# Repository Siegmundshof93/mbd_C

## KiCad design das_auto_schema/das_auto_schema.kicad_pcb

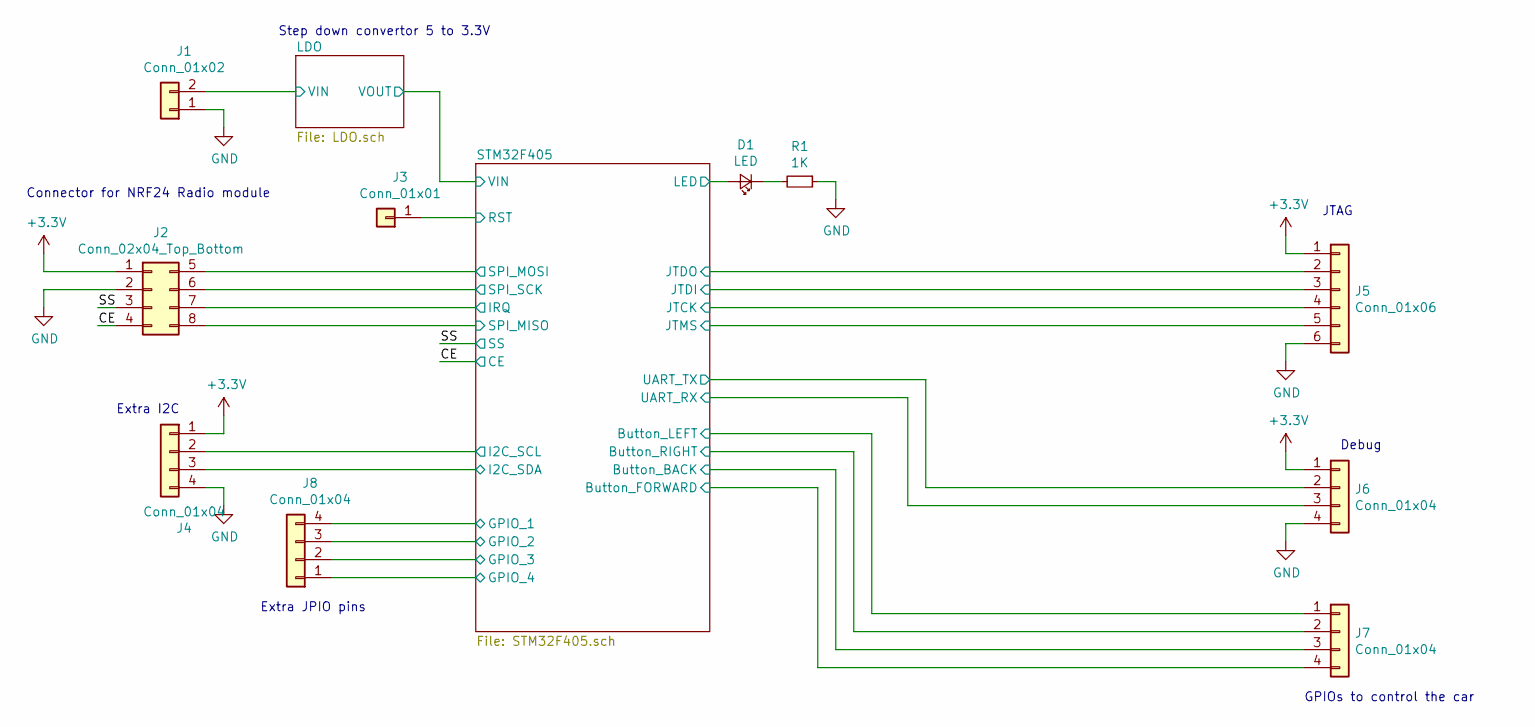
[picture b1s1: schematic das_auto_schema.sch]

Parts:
D1: LED; R_1206_3216Metric
J1: Conn_01x02; PinSocket_1x02_P2.54mm_Vertical
J2: Conn_02x04_Top_Bottom; PinSocket_2x04_P2.54mm_Vertical
J3: Conn_01x01; PinSocket_1x01_P2.54mm_Vertical
J4, J6, J7, J8: Conn_01x04; PinSocket_1x04_P2.54mm_Vertical
J5: Conn_01x06; PinSocket_1x06_P2.54mm_Vertical
R1: 1K; R_0805_2012Metric

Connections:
+3V3: J2.1, J4.1, J5.1, J6.1; also elsewhere on the board
/CE: J2.4; also elsewhere on the board
/LDO/VIN: J1.2; also elsewhere on the board
/SS: J2.3; also elsewhere on the board
/STM32F405/Button_BACK: J7.3; also elsewhere on the board
/STM32F405/Button_FORWARD: J7.4; also elsewhere on the board
/STM32F405/Button_LEFT: J7.1; also elsewhere on the board
/STM32F405/Button_RIGHT: J7.2; also elsewhere on the board
/STM32F405/GPIO_1: J8.4; also elsewhere on the board
/STM32F405/GPIO_2: J8.3; also elsewhere on the board
/STM32F405/GPIO_3: J8.2; also elsewhere on the board
/STM32F405/GPIO_4: J8.1; also elsewhere on the board
/STM32F405/I2C_SCL: J4.2; also elsewhere on the board
/STM32F405/I2C_SDA: J4.3; also elsewhere on the board
/STM32F405/IRQ: J2.7; also elsewhere on the board
/STM32F405/JTCK: J5.4; also elsewhere on the board
/STM32F405/JTDI: J5.3; also elsewhere on the board
/STM32F405/JTDO: J5.2; also elsewhere on the board
/STM32F405/JTMS: J5.5; also elsewhere on the board
/STM32F405/LED: D1.2 (A); also elsewhere on the board
/STM32F405/RST: J3.1; also elsewhere on the board
/STM32F405/SPI_MISO: J2.8; also elsewhere on the board
/STM32F405/SPI_MOSI: J2.5; also elsewhere on the board
/STM32F405/SPI_SCK: J2.6; also elsewhere on the board
/STM32F405/UART_RX: J6.3; also elsewhere on the board
/STM32F405/UART_TX: J6.2; also elsewhere on the board
GND: J1.1, J2.2, J4.4, J5.6, J6.4, R1.1; also elsewhere on the board
unnamed: D1.1 (K), R1.2

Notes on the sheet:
Connector for NRF24 Radio module
JTAG
Extra JPIO pins
GPIOs to control the car
Debug
Step down convertor 5 to 3.3V
Extra I2C

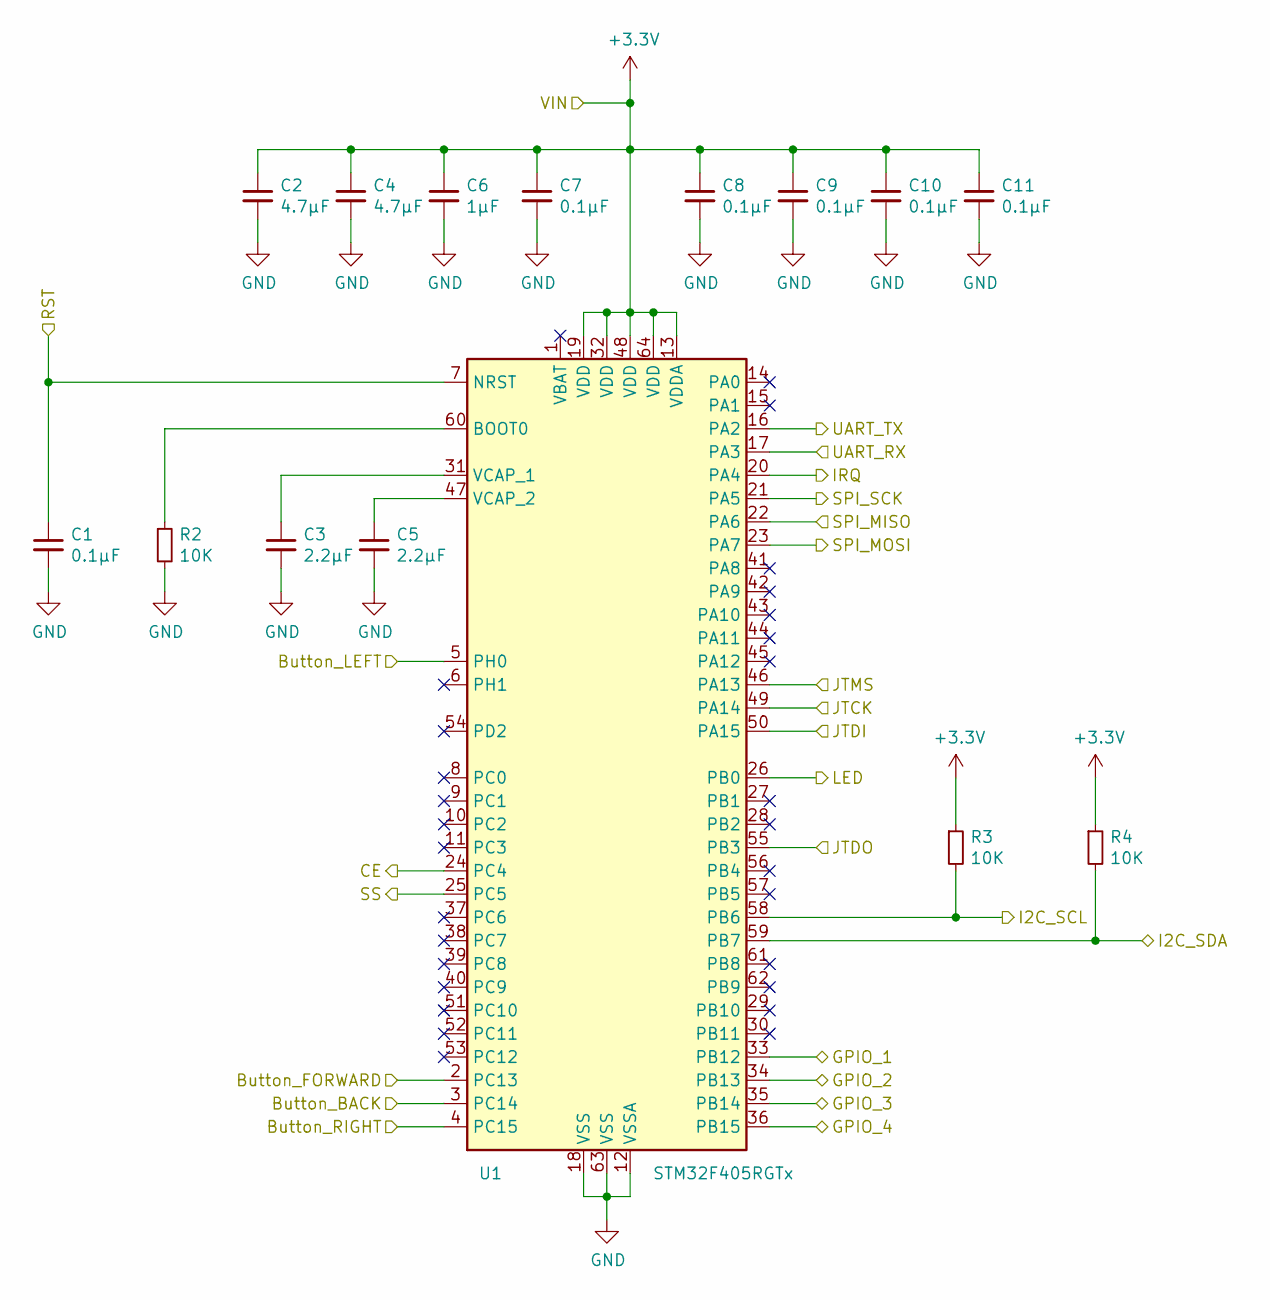
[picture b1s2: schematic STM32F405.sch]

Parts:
C1, C7, C8, C9, C10, C11: 0.1µF; R_0805_2012Metric
C2, C4: 4.7µF; R_0805_2012Metric
C3, C5: 2.2µF; R_0805_2012Metric
C6: 1µF; R_0805_2012Metric
R2, R3, R4: 10K; R_0805_2012Metric
U1: STM32F405RGTx; LQFP-64_10x10mm_P0.5mm

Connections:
+3V3: C2.1, C4.1, C6.1, C7.1, C8.1, C9.1, C10.1, C11.1, R3.1, R4.1, U1.13 (VDDA), U1.19 (VDD), U1.32 (VDD), U1.48 (VDD), U1.64 (VDD); also elsewhere on the board
/CE: U1.24 (PC4); also elsewhere on the board
/SS: U1.25 (PC5); also elsewhere on the board
/STM32F405/Button_BACK: U1.3 (PC14); also elsewhere on the board
/STM32F405/Button_FORWARD: U1.2 (PC13); also elsewhere on the board
/STM32F405/Button_LEFT: U1.5 (PH0); also elsewhere on the board
/STM32F405/Button_RIGHT: U1.4 (PC15); also elsewhere on the board
/STM32F405/GPIO_1: U1.33 (PB12); also elsewhere on the board
/STM32F405/GPIO_2: U1.34 (PB13); also elsewhere on the board
/STM32F405/GPIO_3: U1.35 (PB14); also elsewhere on the board
/STM32F405/GPIO_4: U1.36 (PB15); also elsewhere on the board
/STM32F405/I2C_SCL: R3.2, U1.58 (PB6); also elsewhere on the board
/STM32F405/I2C_SDA: R4.2, U1.59 (PB7); also elsewhere on the board
/STM32F405/IRQ: U1.20 (PA4); also elsewhere on the board
/STM32F405/JTCK: U1.49 (PA14); also elsewhere on the board
/STM32F405/JTDI: U1.50 (PA15); also elsewhere on the board
/STM32F405/JTDO: U1.55 (PB3); also elsewhere on the board
/STM32F405/JTMS: U1.46 (PA13); also elsewhere on the board
/STM32F405/LED: U1.26 (PB0); also elsewhere on the board
/STM32F405/RST: C1.1, U1.7 (NRST); also elsewhere on the board
/STM32F405/SPI_MISO: U1.22 (PA6); also elsewhere on the board
/STM32F405/SPI_MOSI: U1.23 (PA7); also elsewhere on the board
/STM32F405/SPI_SCK: U1.21 (PA5); also elsewhere on the board
/STM32F405/UART_RX: U1.17 (PA3); also elsewhere on the board
/STM32F405/UART_TX: U1.16 (PA2); also elsewhere on the board
GND: C1.2, C2.2, C3.2, C4.2, C5.2, C6.2, C7.2, C8.2, C9.2, C10.2, C11.2, R2.2, U1.12 (VSSA), U1.18 (VSS), U1.63 (VSS); also elsewhere on the board
unnamed: C3.1, U1.31 (VCAP_1)
unnamed: C5.1, U1.47 (VCAP_2)
unnamed: R2.1, U1.60 (BOOT0)

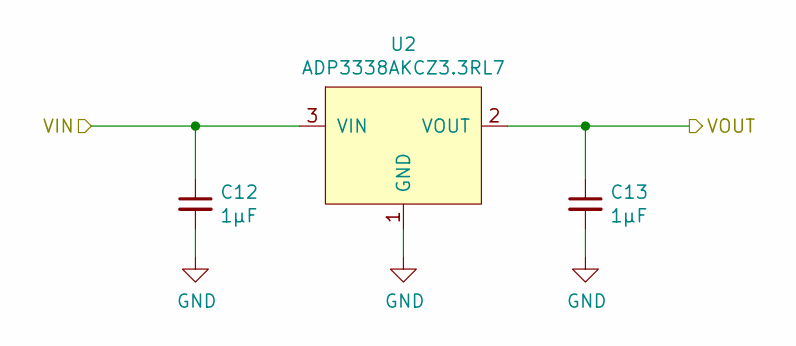
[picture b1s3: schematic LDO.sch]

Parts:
C12, C13: 1µF; R_0805_2012Metric
U2: ADP3338AKCZ3.3RL7; SOT-223-3_TabPin2

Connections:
+3V3: C13.1, U2.2 (VOUT); also elsewhere on the board
/LDO/VIN: C12.1, U2.3 (VIN); also elsewhere on the board
GND: C12.2, C13.2, U2.1 (GND); also elsewhere on the board

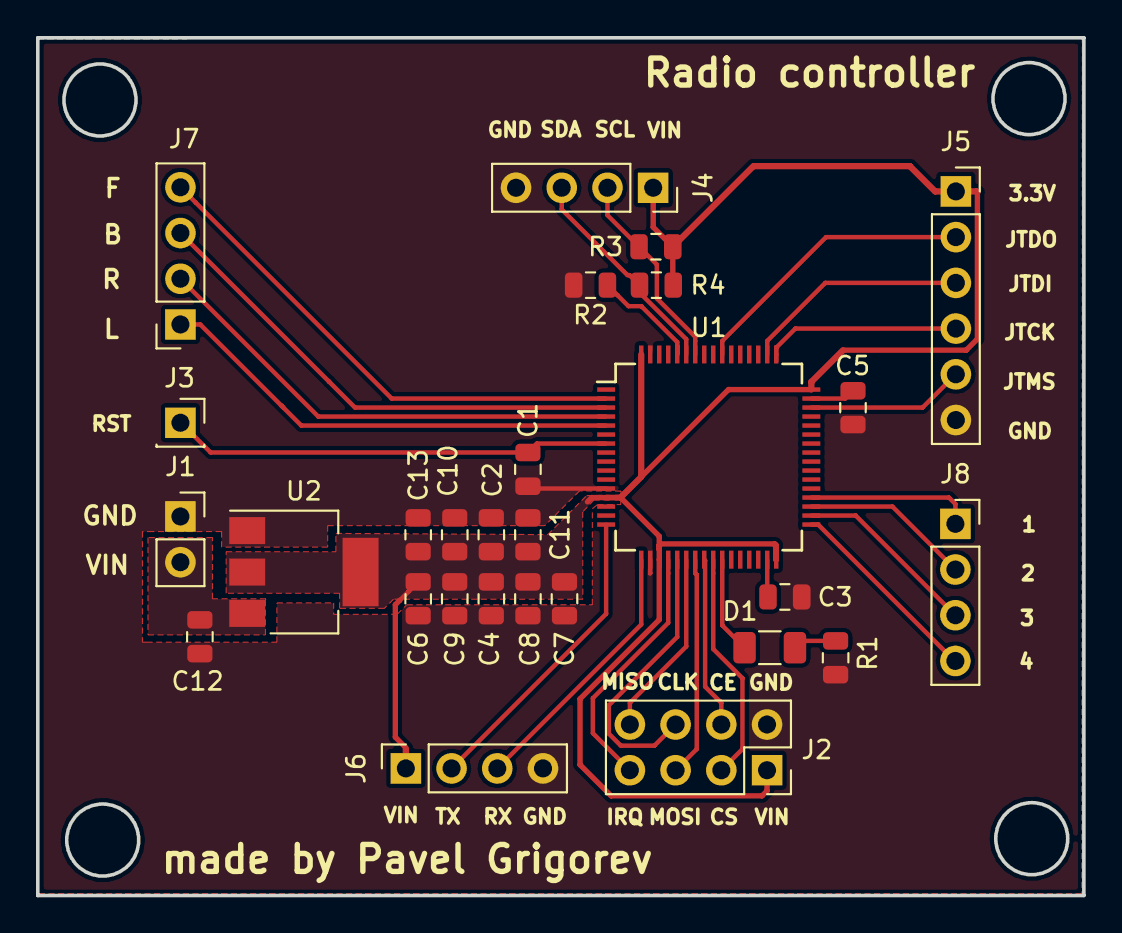
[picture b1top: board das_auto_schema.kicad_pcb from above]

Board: 2 copper layers, 58.1 x 47.7 mm, 28 parts (0 on the bottom side), 31 nets.

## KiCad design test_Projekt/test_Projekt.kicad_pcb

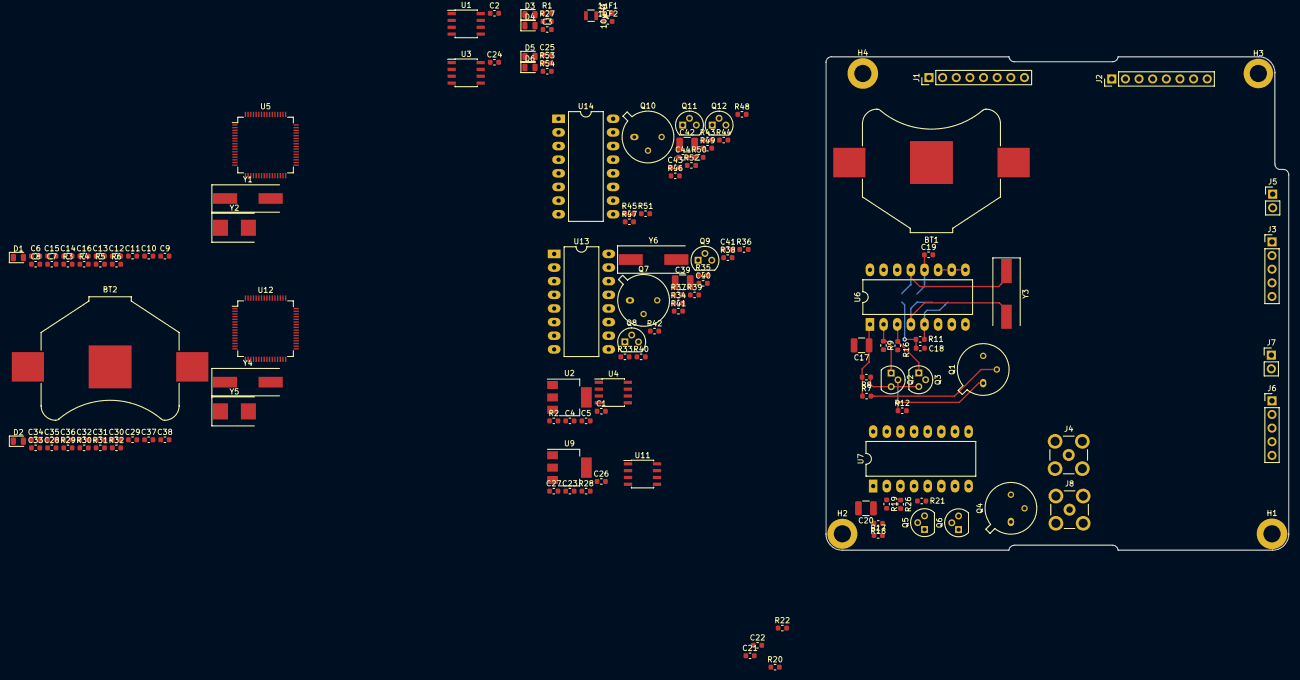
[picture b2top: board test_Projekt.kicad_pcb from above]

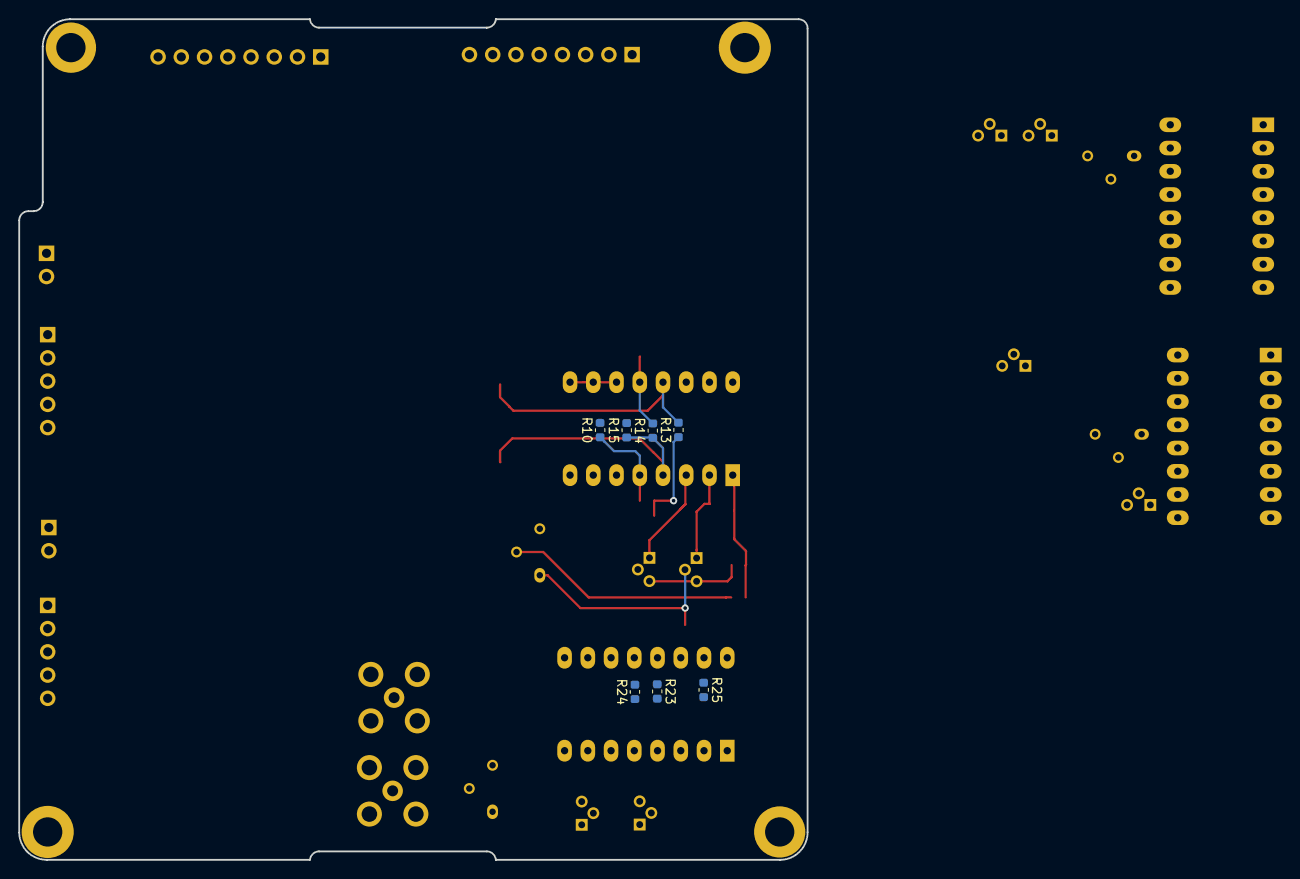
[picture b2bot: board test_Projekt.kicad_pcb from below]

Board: 2 copper layers, 86.2 x 91.9 mm, 151 parts (7 on the bottom side), 96 nets.

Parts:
1µF1, 1µF2: C_Small; C_0603_1608Metric
10µH1: L_Small; L_0806_2016Metric
BT1, BT2: Battery_Cell; BatteryHolder_Keystone_3008_1x2450
C1, C2, C3, C5, C7, C12, C13, C14, C15, C16, C18, C19, C21, C22, C23, C24, C25, C27, C29, C34, C35, C36, C37, C38, C40, C41, C43, C44: 0.1µF; C_0603_1608Metric
C4, C26: 10µF; C_0603_1608Metric
C6, C9, C28, C31: C_Small; C_0603_1608Metric
C8, C10, C30, C32: 9pF; C_0603_1608Metric
C11, C33: 4.7µF; C_0603_1608Metric
C17, C20, C39, C42: 1000; C_1210_3225Metric
D1, D2, D3, D4, D5, D6: LED_Small; LED_0805_2012Metric
H1, H4: MountingHole_Pad; MountingHole_3.2mm_M3_ISO7380_Pad
H2: MountingHole_Pad; MountingHole_3.2mm_M3_DIN965_Pad
H3: MountingHole_Pad; MountingHole_3.2mm_M3_ISO14580_Pad
J1, J2: Conn_01x08_Female; PinHeader_1x08_P2.54mm_Vertical
J3, J6: Conn_01x05_Female; PinHeader_1x05_P2.54mm_Vertical
J4, J8: Conn_01x02; SMB_Jack_Vertical
J5, J7: Conn_01x02_Female; PinHeader_1x02_P2.54mm_Vertical
Q1, Q4, Q7, Q10: Q_NPN_BCE; TO-5-3
Q2, Q3, Q5, Q6, Q8, Q9, Q11, Q12: Q_PNP_BCE; TO-92
R1, R5, R27, R31, R53, R54: 1k; R_0603_1608Metric
R2, R28: 0; R_0603_1608Metric
R3, R4, R6, R29, R30, R32: 10k; R_0603_1608Metric
R7, R17, R33, R43: 270; R_0603_1608Metric
R8, R18, R34, R44: 91; R_0603_1608Metric
R9, R16, R19, R26, R35, R42, R45, R52: 150; R_0603_1608Metric
R10, R15, R20, R25, R36, R41, R46, R51: 100; R_0603_1608Metric
R11, R21, R37, R47: 4.7k; R_0603_1608Metric
R12, R22, R38, R48: 200; R_0603_1608Metric
R13, R23, R39, R49: 10; R_0603_1608Metric
R14, R24, R40, R50: 5.1k; R_0603_1608Metric
U1, U3: 24LC512; SOIC-8_3.9x4.9mm_P1.27mm
U2, U9: LD1117S50TR_SOT223; SOT-223-3_TabPin2
U4, U11: TJA1051T; SOIC-8_3.9x4.9mm_P1.27mm
U5, U12: STM32L476RGTx; LQFP-64_10x10mm_P0.5mm
U6, U7, U13, U14: K500LP216; DIP-16_W10.16mm_LongPads
Y1, Y4: 8MHz; Crystal_SMD_HC49-SD
Y2, Y5: 32.768KHz; Crystal_SMD_FOX_FQ7050-2Pin_7.0x5.0mm
Y3, Y6: Crystal_Small; Crystal_SMD_HC49-SD

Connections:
+3V3: C2.1, C4.1, C11.1, C12.1, C13.1, C14.1, C15.1, C16.1, C24.1, C26.1, C33.1, C34.1, C35.1, C36.1, C37.1, C38.1, J3.1, J6.1, R2.2, R4.1, R6.1, R28.2, R30.1, R32.1, U1.8, U2.2, U3.8, U5.13, U5.19, U5.32, U5.48, U5.64, U9.2, U12.13, U12.19, U12.32, U12.48, U12.64
+5V: 1µF1.1, 10µH1.1, C1.1, C5.1, C17.1, C20.1, C23.1, C27.1, C39.1, C42.1, J2.1, J2.2, R7.1, R8.2, R17.1, R18.2, R33.1, R34.2, R43.1, R44.2, U2.3, U4.3, U6.1, U6.16, U7.1, U7.16, U9.3, U11.3, U13.1, U13.16, U14.1, U14.16
/CANH_1: J1.1, U4.7
/CANH_2: J1.3, U11.7
/CANL_1: J1.2, U4.6
/CANL_2: J1.4, U11.6
/SCL_1: J2.3, R30.2, U3.6, U12.61
/SCL_2: J2.5, R4.2, U1.6, U5.61
/SDA_1: J2.4, R32.2, U3.5, U12.62
/SDA_2: J2.6, R6.2, U1.5, U5.62
/system1/sheet63822154/CAN_RX: U4.4, U5.44
/system1/sheet63822154/CAN_TX: U4.1, U5.45
/system1/sheet63822154/NRST: C7.1, J3.2, U5.7
/system1/sheet63822154/SW_CLK: J3.4, U5.49
/system1/sheet63822154/SW_DIO: J3.3, U5.46
/system1/sheet63822154/UART_RX: J5.2, U5.17
/system1/sheet63822154/UART_TX: J5.1, U5.16
/system1/sheet63822155/Freq_output_CLK: Q1.2, R7.2, U5.15
/system1/sheet63822155/quartz_input_1: R13.1, U6.13, Y3.1
/system1/sheet63822155/quartz_input_2: R14.1, R15.1, U6.4, U6.15, Y3.2
/system1/sheet63822156/Freq_output_CLK: Q4.2, R17.2, U5.14
/system1/sheet63822156/quartz_input_1: J4.2, R23.1, U7.13
/system1/sheet63822156/quartz_input_2: J4.1, R24.1, R25.1, U7.4, U7.15
/system2/sheet63824A8A/CAN_RX: U11.4, U12.44
/system2/sheet63824A8A/CAN_TX: U11.1, U12.45
/system2/sheet63824A8A/NRST: C29.1, J6.2, U12.7
/system2/sheet63824A8A/SW_CLK: J6.4, U12.49
/system2/sheet63824A8A/SW_DIO: J6.3, U12.46
/system2/sheet63824A8A/UART_RX: J7.2, U12.17
/system2/sheet63824A8A/UART_TX: J7.1, U12.16
/system2/sheet63824A8B/Freq_output_CLK: Q7.2, R33.2, U12.15
/system2/sheet63824A8B/quartz_input_1: R39.1, U13.13, Y6.1
/system2/sheet63824A8B/quartz_input_2: R40.1, R41.1, U13.4, U13.15, Y6.2
/system2/sheet63824A8C/Freq_output_CLK: Q10.2, R43.2, U12.14
/system2/sheet63824A8C/quartz_input_1: J8.2, R49.1, U14.13
/system2/sheet63824A8C/quartz_input_2: J8.1, R50.1, R51.1, U14.4, U14.15
GND: 1µF1.2, 1µF2.2, BT1.2, BT2.2, C1.2, C2.2, C3.2, C4.2, C5.2, C6.2, C7.2, C8.2, C9.2, C10.1, C11.2, C12.2, C13.2, C14.2, C15.2, C16.2, C17.2, C18.2, C19.2, C20.2, C21.2, C22.2, C23.2, C24.2, C25.2, C26.2, C27.2, C28.2, C29.2, C30.2, C31.2, C32.1, C33.2, C34.2, C35.2, C36.2, C37.2, C38.2, C39.2, C40.2, C41.2, C42.2, C43.2, C44.2, H1.1, H2.1, H3.1, H4.1, J1.7, J1.8, J2.7, J2.8, J3.5, J6.5, Q1.3, Q3.2, Q4.3, Q6.2, Q7.3, Q9.2, Q10.3, Q12.2, R1.2, R3.2, R5.2, R9.2, R10.2, R12.2, R15.2, R16.2, R19.2, R20.2, R22.2, R25.2, R26.2, R27.2, R29.2, R31.2, R35.2, R36.2, R38.2, R41.2, R42.2, R45.2, R46.2, R48.2, R51.2, R52.2, R53.2, R54.2, U1.1, U1.2, U1.3, U1.4, U1.7, U2.1, U3.1, U3.2, U3.3, U3.4, U3.7, U4.2, U5.12, U5.18, U5.31, U5.47, U5.63, U6.8, U7.8, U9.1, U11.2, U12.12, U12.18, U12.31, U12.47, U12.63, U13.8, U14.8
unnamed: 1µF2.1, 10µH1.2, J1.5, J1.6
unnamed: BT1.1, C3.1, U5.1
unnamed: BT2.1, C25.1, U12.1
unnamed: C6.1, U5.5, Y1.1
unnamed: C8.1, U5.3, Y2.1
unnamed: C9.1, U5.6, Y1.2
unnamed: C10.2, U5.4, Y2.2
unnamed: C18.1, R11.2, R13.2
unnamed: C19.1, R14.2, U6.12
unnamed: C21.1, R21.2, R23.2
unnamed: C22.1, R24.2, U7.12
unnamed: C28.1, U12.5, Y4.1
unnamed: C30.1, U12.3, Y5.1
unnamed: C31.1, U12.6, Y4.2
unnamed: C32.2, U12.4, Y5.2
unnamed: C40.1, R37.2, R39.2
unnamed: C41.1, R40.2, U13.12
unnamed: C43.1, R47.2, R49.2
unnamed: C44.1, R50.2, U14.12
unnamed: D1.1, R5.1
unnamed: D1.2, U5.21
unnamed: D2.1, R31.1
unnamed: D2.2, U12.21
unnamed: D3.1, R1.1
unnamed: D3.2, U5.22
unnamed: D4.1, R27.1
unnamed: D4.2, U5.23
unnamed: D5.1, R53.1
unnamed: D5.2, U12.22
unnamed: D6.1, R54.1
unnamed: D6.2, U12.23
unnamed: Q1.1, Q2.2, R12.1
unnamed: Q2.1, R9.1, U6.2
unnamed: Q2.3, Q3.3, R8.1
unnamed: Q3.1, R16.1, U6.3
unnamed: Q4.1, Q5.2, R22.1
unnamed: Q5.1, R19.1, U7.2
unnamed: Q5.3, Q6.3, R18.1
unnamed: Q6.1, R26.1, U7.3
unnamed: Q7.1, Q8.2, R38.1
unnamed: Q8.1, R35.1, U13.2
unnamed: Q8.3, Q9.3, R34.1
unnamed: Q9.1, R42.1, U13.3
unnamed: Q10.1, Q11.2, R48.1
unnamed: Q11.1, R45.1, U14.2
unnamed: Q11.3, Q12.3, R44.1
unnamed: Q12.1, R52.1, U14.3
unnamed: R2.1, U4.8
unnamed: R3.1, U5.60
unnamed: R10.1, R11.1, U6.5, U6.14
unnamed: R20.1, R21.1, U7.5, U7.14
unnamed: R28.1, U11.8
unnamed: R29.1, U12.60
unnamed: R36.1, R37.1, U13.5, U13.14
unnamed: R46.1, R47.1, U14.5, U14.14
unnamed: U6.9, U6.10, U6.11
unnamed: U7.9, U7.10, U7.11
unnamed: U13.9, U13.10, U13.11
unnamed: U14.9, U14.10, U14.11

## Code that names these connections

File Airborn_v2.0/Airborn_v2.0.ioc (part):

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Mcu.Name=STM32F030C8Tx
Mcu.Package=LQFP48
Mcu.UserName=STM32F030C8Tx
PA10.Mode=Asynchronous
PA10.Signal=USART1_RX
PA13.Mode=Serial_Wire
PA13.Signal=SYS_SWDIO
PA14.Mode=Serial_Wire
PA14.Signal=SYS_SWCLK
PA2.Mode=Asynchronous
PA2.Signal=USART2_TX
PA3.Mode=Asynchronous
PA3.Signal=USART2_RX
PA5.Mode=Full_Duplex_Master
PA5.Signal=SPI1_SCK
PA6.Mode=Full_Duplex_Master
PA6.Signal=SPI1_MISO
PA7.Mode=Full_Duplex_Master
PA7.Signal=SPI1_MOSI
PA9.Mode=Asynchronous
PA9.Signal=USART1_TX
PB0.GPIOParameters=GPIO_Label
PB0.GPIO_Label=LoRa_CS
PB0.Signal=GPIO_Output
PB1.GPIOParameters=GPIO_Label
PB1.GPIO_Label=LoRa_RESET
PB1.Signal=GPIO_Output
PB12.Signal=GPIO_Output
PB13.Signal=GPIO_Output
PB14.Signal=GPIO_Output
PB2.GPIOParameters=GPIO_Label
PB2.GPIO_Label=LoRA_DIO0
PB2.Signal=GPIO_Output
PB6.Mode=I2C
PB6.Signal=I2C1_SCL
PB7.Mode=I2C
PB7.Signal=I2C1_SDA
RCC.SYSCLKFreq_VALUE=40000000
RCC.SYSCLKSource=RCC_SYSCLKSOURCE_PLLCLK
board=custom

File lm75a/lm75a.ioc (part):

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Mcu.Name=STM32L073R(B-Z)Tx
Mcu.Package=LQFP64
Mcu.UserName=STM32L073RZTx
PA10.Mode=I2C
PA10.Signal=I2C1_SDA
PA13.GPIOParameters=GPIO_Label
PA13.GPIO_Label=TMS
PA13.Signal=SYS_SWDIO
PA14.GPIOParameters=GPIO_Label
PA14.GPIO_Label=TCK
PA14.Signal=SYS_SWCLK
PA2.GPIOParameters=GPIO_Label
PA2.GPIO_Label=USART_TX
PA2.Mode=Asynchronous
PA2.Signal=USART2_TX
PA3.GPIOParameters=GPIO_Label
PA3.GPIO_Label=USART_RX
PA3.Mode=Asynchronous
PA3.Signal=USART2_RX
PA5.GPIOParameters=GPIO_Label
PA5.GPIO_Label=LD2 [Green Led]
PA5.Signal=GPIO_Output
PA9.Mode=I2C
PA9.Signal=I2C1_SCL
PC13.GPIOParameters=GPIO_Label,GPIO_ModeDefaultEXTI
PC13.GPIO_Label=B1 [Blue PushButton]
PC13.GPIO_ModeDefaultEXTI=GPIO_MODE_IT_FALLING
PC13.Signal=GPXTI13
PC14-OSC32_IN.Signal=RCC_OSC32_IN
PC15-OSC32_OUT.Signal=RCC_OSC32_OUT
PH0-OSC_IN.GPIOParameters=GPIO_Label
PH0-OSC_IN.GPIO_Label=MCO
PH0-OSC_IN.Signal=RCC_OSC_IN
RCC.HSE_VALUE=8000000
RCC.SYSCLKFreq_VALUE=16000000
RCC.SYSCLKSource=RCC_SYSCLKSOURCE_HSI
board=NUCLEO-L073RZ
boardIOC=true

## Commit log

2020-12-07 das auto first commit
2020-12-07 beautiful program
2020-12-21 compelitely working auto with a schematic of the controller
2021-03-24 added LUX+W25Q, NRF24TX, lm75-termosensor
2021-05-11 Added IMU + python script for realtime plot + Kicad updetes
2021-05-27 improved das_auto programm (not ugly and readable)
2021-06-24 can TX and can Rx added (can TX for extended ID for DecoR)
2021-08-24 added LoRa mbed
2022-01-30 added new file with airborn code (LoRa + GPS that works on NMEA)
2022-01-31 termo equivalent for Orbital systems tests
2022-06-04 added new folder for a Payload
2022-06-25 add eeprom
2022-06-28 eeprom with pointer memory write and memory read
2022-08-10 finished progect(first review) added CAN communication
2022-12-23 Airborne Board can send signal with loRa
2023-01-17 Amur project kicad with redundand components
